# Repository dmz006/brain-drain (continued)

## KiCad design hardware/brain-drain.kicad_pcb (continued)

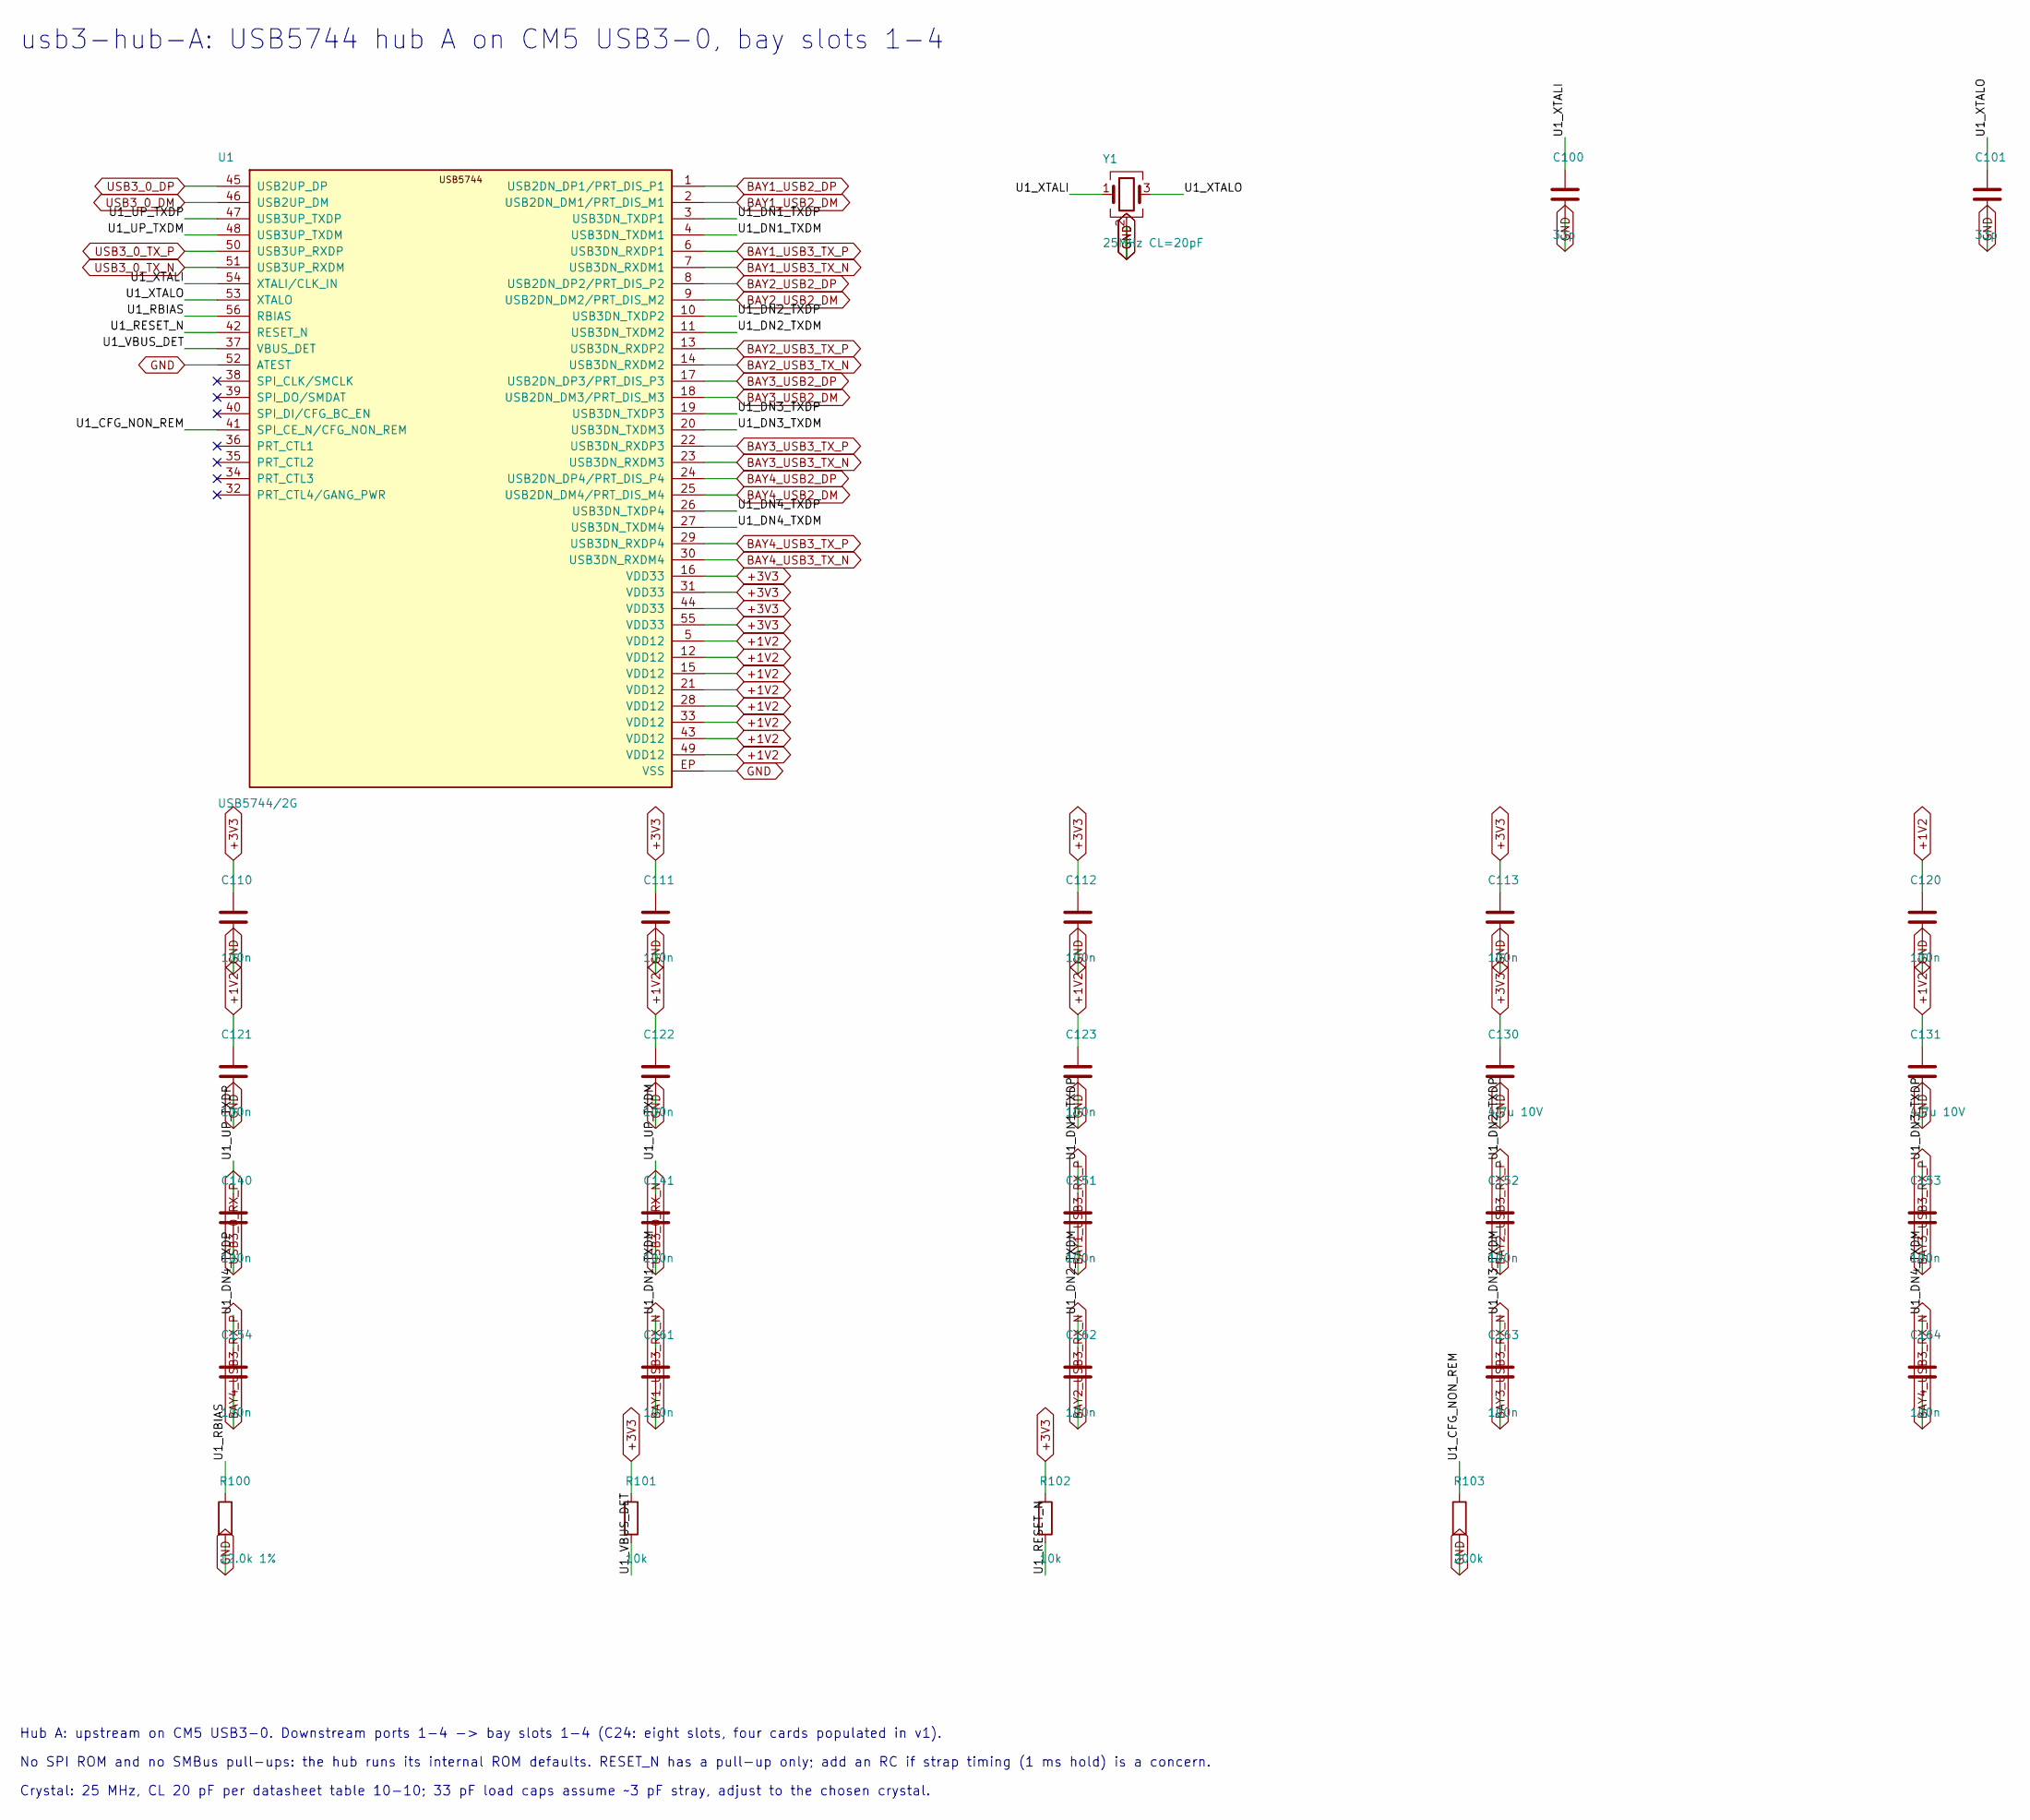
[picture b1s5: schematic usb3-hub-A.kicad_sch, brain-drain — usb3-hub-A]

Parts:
C100, C101: 33p; C_0402_1005Metric
C110, C111, C112, C113, C120, C121, C122, C123, C140, C141, C151, C152, C153, C154, C161, C162, C163, C164: 100n; C_0402_1005Metric
C130, C131: 4.7u 10V; C_0603_1608Metric
R100: 12.0k 1%; R_0402_1005Metric
R101, R102: 10k; R_0402_1005Metric
R103: 200k; R_0402_1005Metric
U1: USB5744/2G; QFN-56-1EP_7x7mm_P0.4mm_EP3.2x3.2mm
Y1: 25MHz CL=20pF; Crystal_SMD_3225-4Pin_3.2x2.5mm

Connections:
+1V2: C120.1, C121.1, C122.1, C123.1, C131.1, U1.5 (VDD12), U1.12 (VDD12), U1.15 (VDD12), U1.21 (VDD12), U1.28 (VDD12), U1.33 (VDD12), U1.43 (VDD12), U1.49 (VDD12); also elsewhere on the board
+3V3: C110.1, C111.1, C112.1, C113.1, C130.1, R101.1, R102.1, U1.16 (VDD33), U1.31 (VDD33), U1.44 (VDD33), U1.55 (VDD33); also elsewhere on the board
BAY1_USB2_DM: U1.2 (USB2DN_DM1/PRT_DIS_M1); also elsewhere on the board
BAY1_USB2_DP: U1.1 (USB2DN_DP1/PRT_DIS_P1); also elsewhere on the board
BAY1_USB3_RX_N: C161.2; also elsewhere on the board
BAY1_USB3_RX_P: C151.2; also elsewhere on the board
BAY1_USB3_TX_N: U1.7 (USB3DN_RXDM1); also elsewhere on the board
BAY1_USB3_TX_P: U1.6 (USB3DN_RXDP1); also elsewhere on the board
BAY2_USB2_DM: U1.9 (USB2DN_DM2/PRT_DIS_M2); also elsewhere on the board
BAY2_USB2_DP: U1.8 (USB2DN_DP2/PRT_DIS_P2); also elsewhere on the board
BAY2_USB3_RX_N: C162.2; also elsewhere on the board
BAY2_USB3_RX_P: C152.2; also elsewhere on the board
BAY2_USB3_TX_N: U1.14 (USB3DN_RXDM2); also elsewhere on the board
BAY2_USB3_TX_P: U1.13 (USB3DN_RXDP2); also elsewhere on the board
BAY3_USB2_DM: U1.18 (USB2DN_DM3/PRT_DIS_M3); also elsewhere on the board
BAY3_USB2_DP: U1.17 (USB2DN_DP3/PRT_DIS_P3); also elsewhere on the board
BAY3_USB3_RX_N: C163.2; also elsewhere on the board
BAY3_USB3_RX_P: C153.2; also elsewhere on the board
BAY3_USB3_TX_N: U1.23 (USB3DN_RXDM3); also elsewhere on the board
BAY3_USB3_TX_P: U1.22 (USB3DN_RXDP3); also elsewhere on the board
BAY4_USB2_DM: U1.25 (USB2DN_DM4/PRT_DIS_M4); also elsewhere on the board
BAY4_USB2_DP: U1.24 (USB2DN_DP4/PRT_DIS_P4); also elsewhere on the board
BAY4_USB3_RX_N: C164.2; also elsewhere on the board
BAY4_USB3_RX_P: C154.2; also elsewhere on the board
BAY4_USB3_TX_N: U1.30 (USB3DN_RXDM4); also elsewhere on the board
BAY4_USB3_TX_P: U1.29 (USB3DN_RXDP4); also elsewhere on the board
GND: C100.2, C101.2, C110.2, C111.2, C112.2, C113.2, C120.2, C121.2, C122.2, C123.2, C130.2, C131.2, R100.2, R103.2, U1.52 (ATEST), U1.EP (VSS), Y1.2 (G), Y1.4 (G); also elsewhere on the board
U1_CFG_NON_REM: R103.1, U1.41 (SPI_CE_N/CFG_NON_REM)
U1_DN1_TXDM: C161.1, U1.4 (USB3DN_TXDM1)
U1_DN1_TXDP: C151.1, U1.3 (USB3DN_TXDP1)
U1_DN2_TXDM: C162.1, U1.11 (USB3DN_TXDM2)
U1_DN2_TXDP: C152.1, U1.10 (USB3DN_TXDP2)
U1_DN3_TXDM: C163.1, U1.20 (USB3DN_TXDM3)
U1_DN3_TXDP: C153.1, U1.19 (USB3DN_TXDP3)
U1_DN4_TXDM: C164.1, U1.27 (USB3DN_TXDM4)
U1_DN4_TXDP: C154.1, U1.26 (USB3DN_TXDP4)
U1_RBIAS: R100.1, U1.56 (RBIAS)
U1_RESET_N: R102.2, U1.42 (RESET_N)
U1_UP_TXDM: C141.1, U1.48 (USB3UP_TXDM)
U1_UP_TXDP: C140.1, U1.47 (USB3UP_TXDP)
U1_VBUS_DET: R101.2, U1.37 (VBUS_DET)
U1_XTALI: C100.1, U1.54 (XTALI/CLK_IN), Y1.1
U1_XTALO: C101.1, U1.53 (XTALO), Y1.3
USB3_0_DM: U1.46 (USB2UP_DM); also elsewhere on the board
USB3_0_DP: U1.45 (USB2UP_DP); also elsewhere on the board
USB3_0_RX_N: C141.2; also elsewhere on the board
USB3_0_RX_P: C140.2; also elsewhere on the board
USB3_0_TX_N: U1.51 (USB3UP_RXDM); also elsewhere on the board
USB3_0_TX_P: U1.50 (USB3UP_RXDP); also elsewhere on the board

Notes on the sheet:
usb3-hub-A: USB5744 hub A on CM5 USB3-0, bay slots 1-4
Hub A: upstream on CM5 USB3-0. Downstream ports 1-4 -> bay slots 1-4 (C24: eight slots, four cards populated in v1).
No SPI ROM and no SMBus pull-ups: the hub runs its internal ROM defaults. RESET_N has a pull-up only; add an RC if strap timing (1 ms hold) is a concern.
Crystal: 25 MHz, CL 20 pF per datasheet table 10-10; 33 pF load caps assume ~3 pF stray, adjust to the chosen crystal.

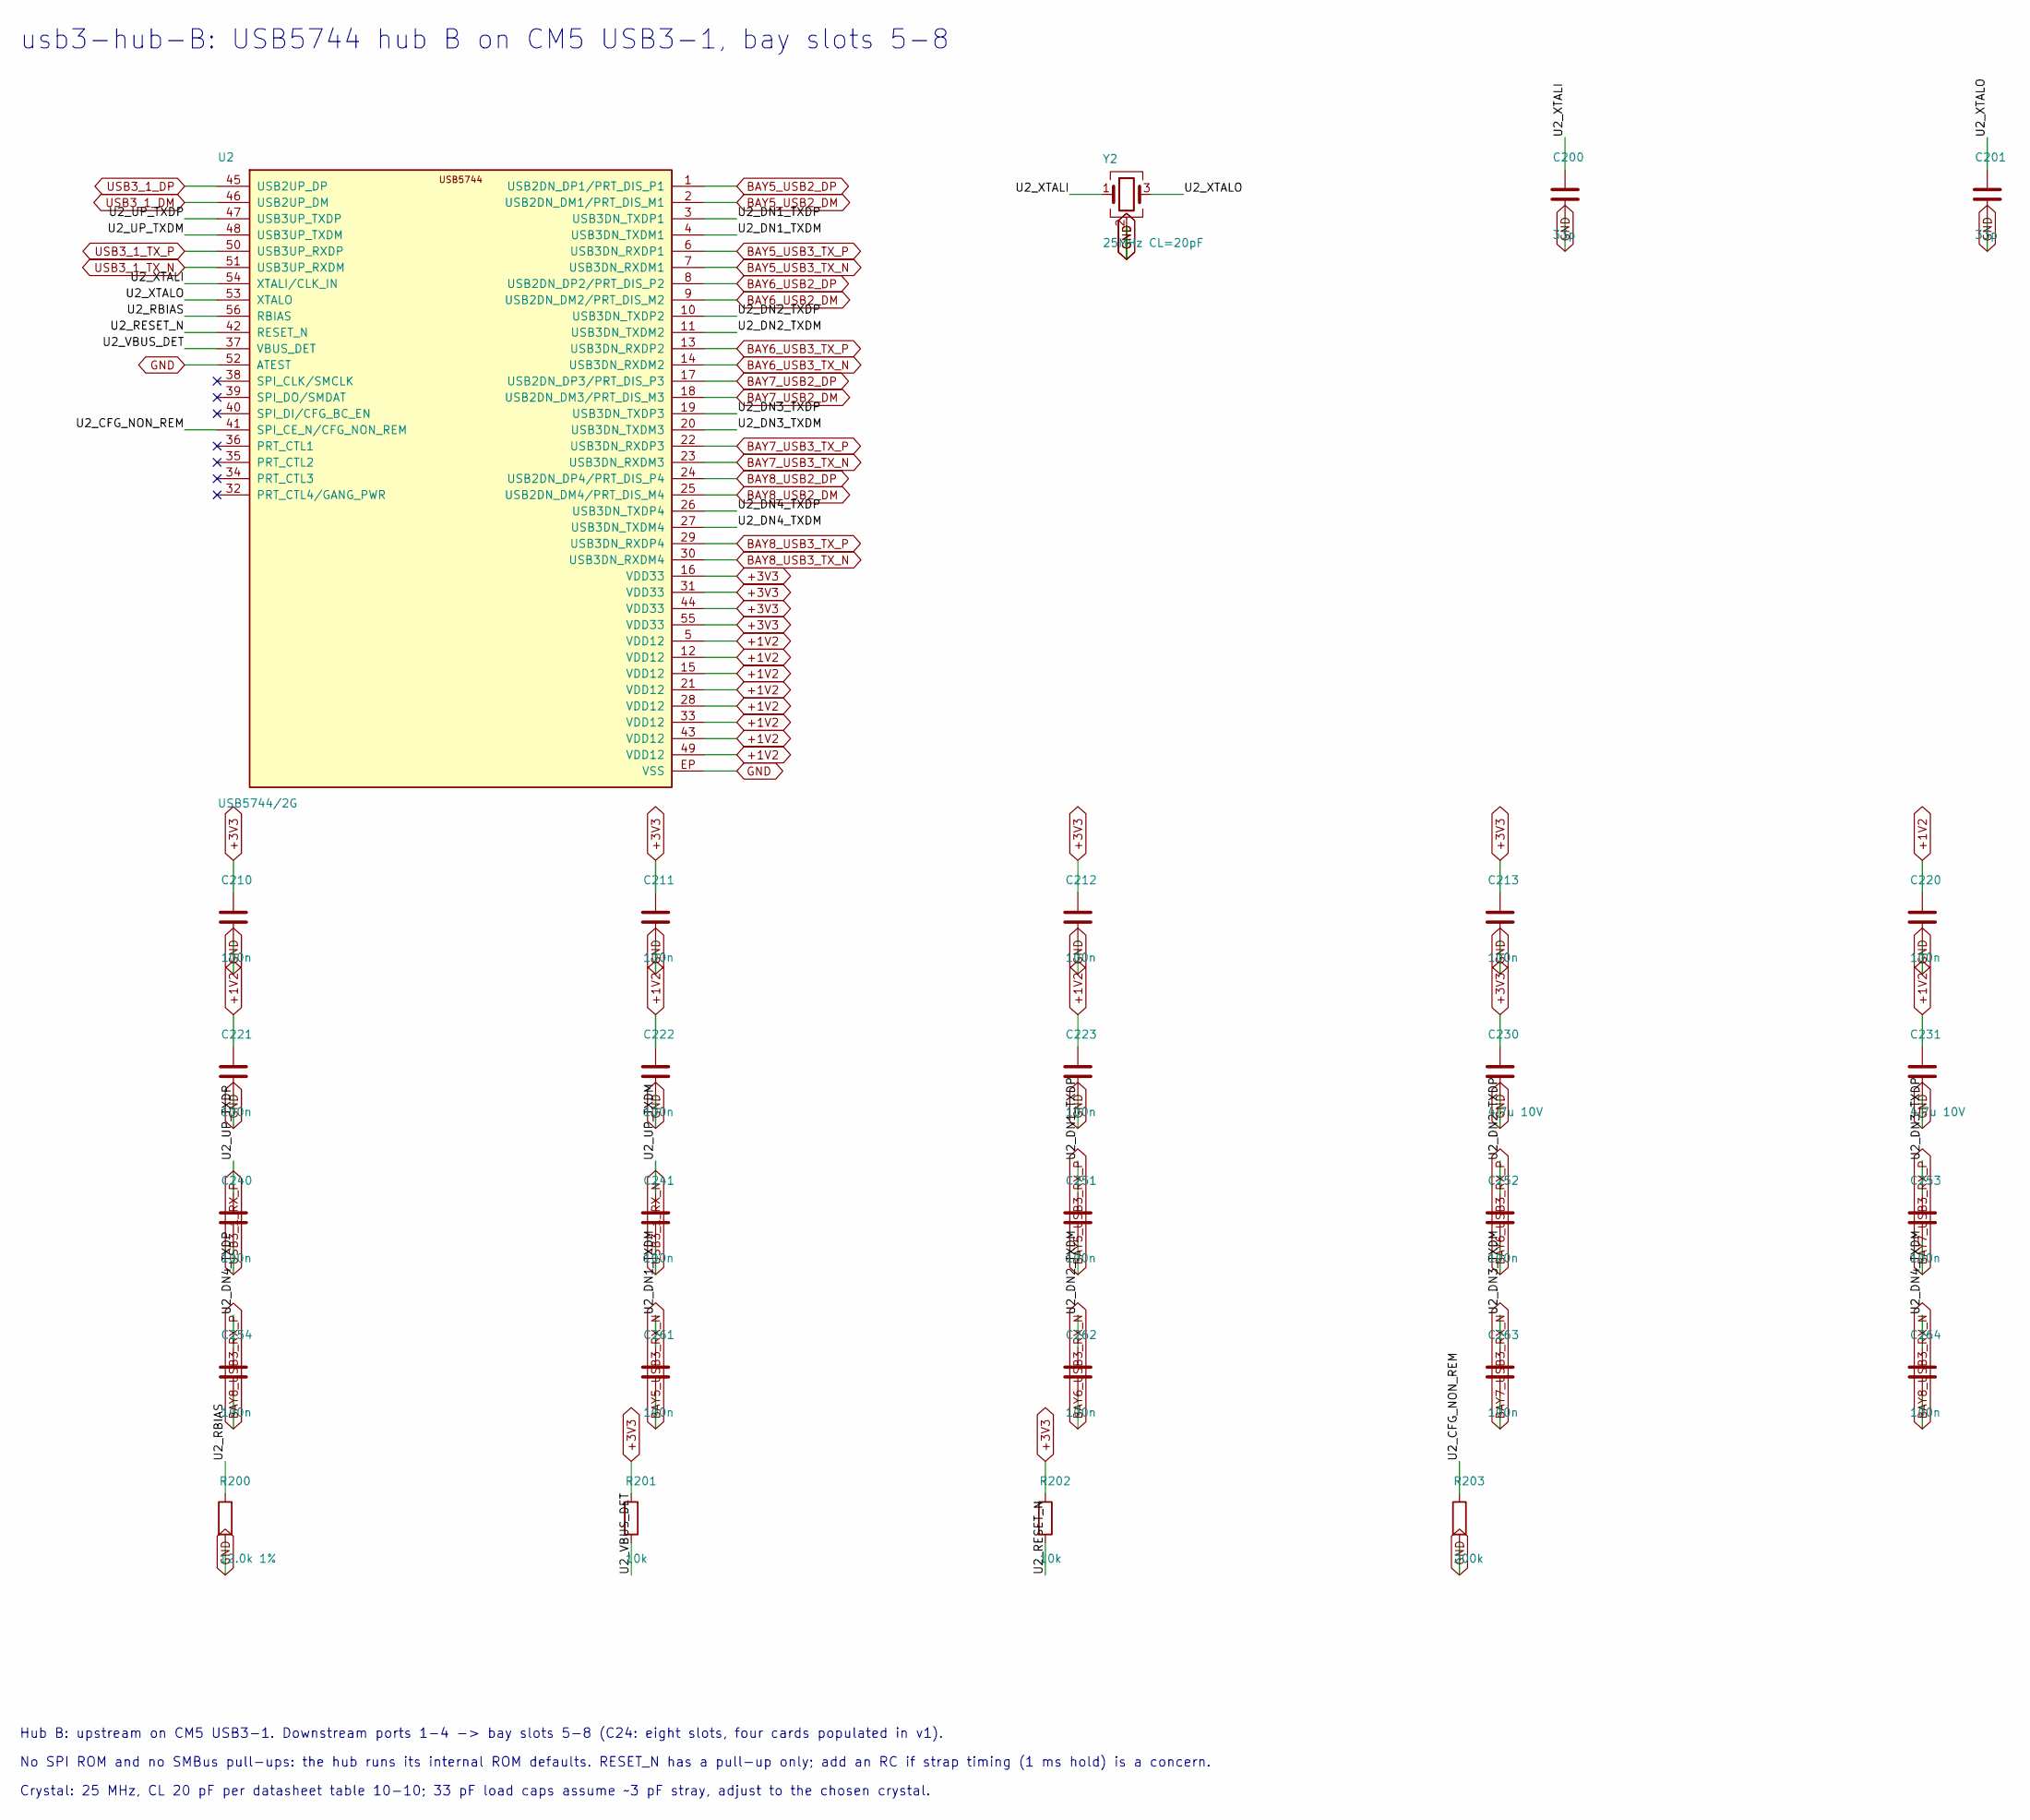
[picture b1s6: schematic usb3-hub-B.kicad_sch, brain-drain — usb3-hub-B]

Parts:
C200, C201: 33p; C_0402_1005Metric
C210, C211, C212, C213, C220, C221, C222, C223, C240, C241, C251, C252, C253, C254, C261, C262, C263, C264: 100n; C_0402_1005Metric
C230, C231: 4.7u 10V; C_0603_1608Metric
R200: 12.0k 1%; R_0402_1005Metric
R201, R202: 10k; R_0402_1005Metric
R203: 200k; R_0402_1005Metric
U2: USB5744/2G; QFN-56-1EP_7x7mm_P0.4mm_EP3.2x3.2mm
Y2: 25MHz CL=20pF; Crystal_SMD_3225-4Pin_3.2x2.5mm

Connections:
+1V2: C220.1, C221.1, C222.1, C223.1, C231.1, U2.5 (VDD12), U2.12 (VDD12), U2.15 (VDD12), U2.21 (VDD12), U2.28 (VDD12), U2.33 (VDD12), U2.43 (VDD12), U2.49 (VDD12); also elsewhere on the board
+3V3: C210.1, C211.1, C212.1, C213.1, C230.1, R201.1, R202.1, U2.16 (VDD33), U2.31 (VDD33), U2.44 (VDD33), U2.55 (VDD33); also elsewhere on the board
BAY5_USB2_DM: U2.2 (USB2DN_DM1/PRT_DIS_M1); also elsewhere on the board
BAY5_USB2_DP: U2.1 (USB2DN_DP1/PRT_DIS_P1); also elsewhere on the board
BAY5_USB3_RX_N: C261.2; also elsewhere on the board
BAY5_USB3_RX_P: C251.2; also elsewhere on the board
BAY5_USB3_TX_N: U2.7 (USB3DN_RXDM1); also elsewhere on the board
BAY5_USB3_TX_P: U2.6 (USB3DN_RXDP1); also elsewhere on the board
BAY6_USB2_DM: U2.9 (USB2DN_DM2/PRT_DIS_M2); also elsewhere on the board
BAY6_USB2_DP: U2.8 (USB2DN_DP2/PRT_DIS_P2); also elsewhere on the board
BAY6_USB3_RX_N: C262.2; also elsewhere on the board
BAY6_USB3_RX_P: C252.2; also elsewhere on the board
BAY6_USB3_TX_N: U2.14 (USB3DN_RXDM2); also elsewhere on the board
BAY6_USB3_TX_P: U2.13 (USB3DN_RXDP2); also elsewhere on the board
BAY7_USB2_DM: U2.18 (USB2DN_DM3/PRT_DIS_M3); also elsewhere on the board
BAY7_USB2_DP: U2.17 (USB2DN_DP3/PRT_DIS_P3); also elsewhere on the board
BAY7_USB3_RX_N: C263.2; also elsewhere on the board
BAY7_USB3_RX_P: C253.2; also elsewhere on the board
BAY7_USB3_TX_N: U2.23 (USB3DN_RXDM3); also elsewhere on the board
BAY7_USB3_TX_P: U2.22 (USB3DN_RXDP3); also elsewhere on the board
BAY8_USB2_DM: U2.25 (USB2DN_DM4/PRT_DIS_M4); also elsewhere on the board
BAY8_USB2_DP: U2.24 (USB2DN_DP4/PRT_DIS_P4); also elsewhere on the board
BAY8_USB3_RX_N: C264.2; also elsewhere on the board
BAY8_USB3_RX_P: C254.2; also elsewhere on the board
BAY8_USB3_TX_N: U2.30 (USB3DN_RXDM4); also elsewhere on the board
BAY8_USB3_TX_P: U2.29 (USB3DN_RXDP4); also elsewhere on the board
GND: C200.2, C201.2, C210.2, C211.2, C212.2, C213.2, C220.2, C221.2, C222.2, C223.2, C230.2, C231.2, R200.2, R203.2, U2.52 (ATEST), U2.EP (VSS), Y2.2 (G), Y2.4 (G); also elsewhere on the board
U2_CFG_NON_REM: R203.1, U2.41 (SPI_CE_N/CFG_NON_REM)
U2_DN1_TXDM: C261.1, U2.4 (USB3DN_TXDM1)
U2_DN1_TXDP: C251.1, U2.3 (USB3DN_TXDP1)
U2_DN2_TXDM: C262.1, U2.11 (USB3DN_TXDM2)
U2_DN2_TXDP: C252.1, U2.10 (USB3DN_TXDP2)
U2_DN3_TXDM: C263.1, U2.20 (USB3DN_TXDM3)
U2_DN3_TXDP: C253.1, U2.19 (USB3DN_TXDP3)
U2_DN4_TXDM: C264.1, U2.27 (USB3DN_TXDM4)
U2_DN4_TXDP: C254.1, U2.26 (USB3DN_TXDP4)
U2_RBIAS: R200.1, U2.56 (RBIAS)
U2_RESET_N: R202.2, U2.42 (RESET_N)
U2_UP_TXDM: C241.1, U2.48 (USB3UP_TXDM)
U2_UP_TXDP: C240.1, U2.47 (USB3UP_TXDP)
U2_VBUS_DET: R201.2, U2.37 (VBUS_DET)
U2_XTALI: C200.1, U2.54 (XTALI/CLK_IN), Y2.1
U2_XTALO: C201.1, U2.53 (XTALO), Y2.3
USB3_1_DM: U2.46 (USB2UP_DM); also elsewhere on the board
USB3_1_DP: U2.45 (USB2UP_DP); also elsewhere on the board
USB3_1_RX_N: C241.2; also elsewhere on the board
USB3_1_RX_P: C240.2; also elsewhere on the board
USB3_1_TX_N: U2.51 (USB3UP_RXDM); also elsewhere on the board
USB3_1_TX_P: U2.50 (USB3UP_RXDP); also elsewhere on the board

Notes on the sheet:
usb3-hub-B: USB5744 hub B on CM5 USB3-1, bay slots 5-8
Hub B: upstream on CM5 USB3-1. Downstream ports 1-4 -> bay slots 5-8 (C24: eight slots, four cards populated in v1).
No SPI ROM and no SMBus pull-ups: the hub runs its internal ROM defaults. RESET_N has a pull-up only; add an RC if strap timing (1 ms hold) is a concern.
Crystal: 25 MHz, CL 20 pF per datasheet table 10-10; 33 pF load caps assume ~3 pF stray, adjust to the chosen crystal.

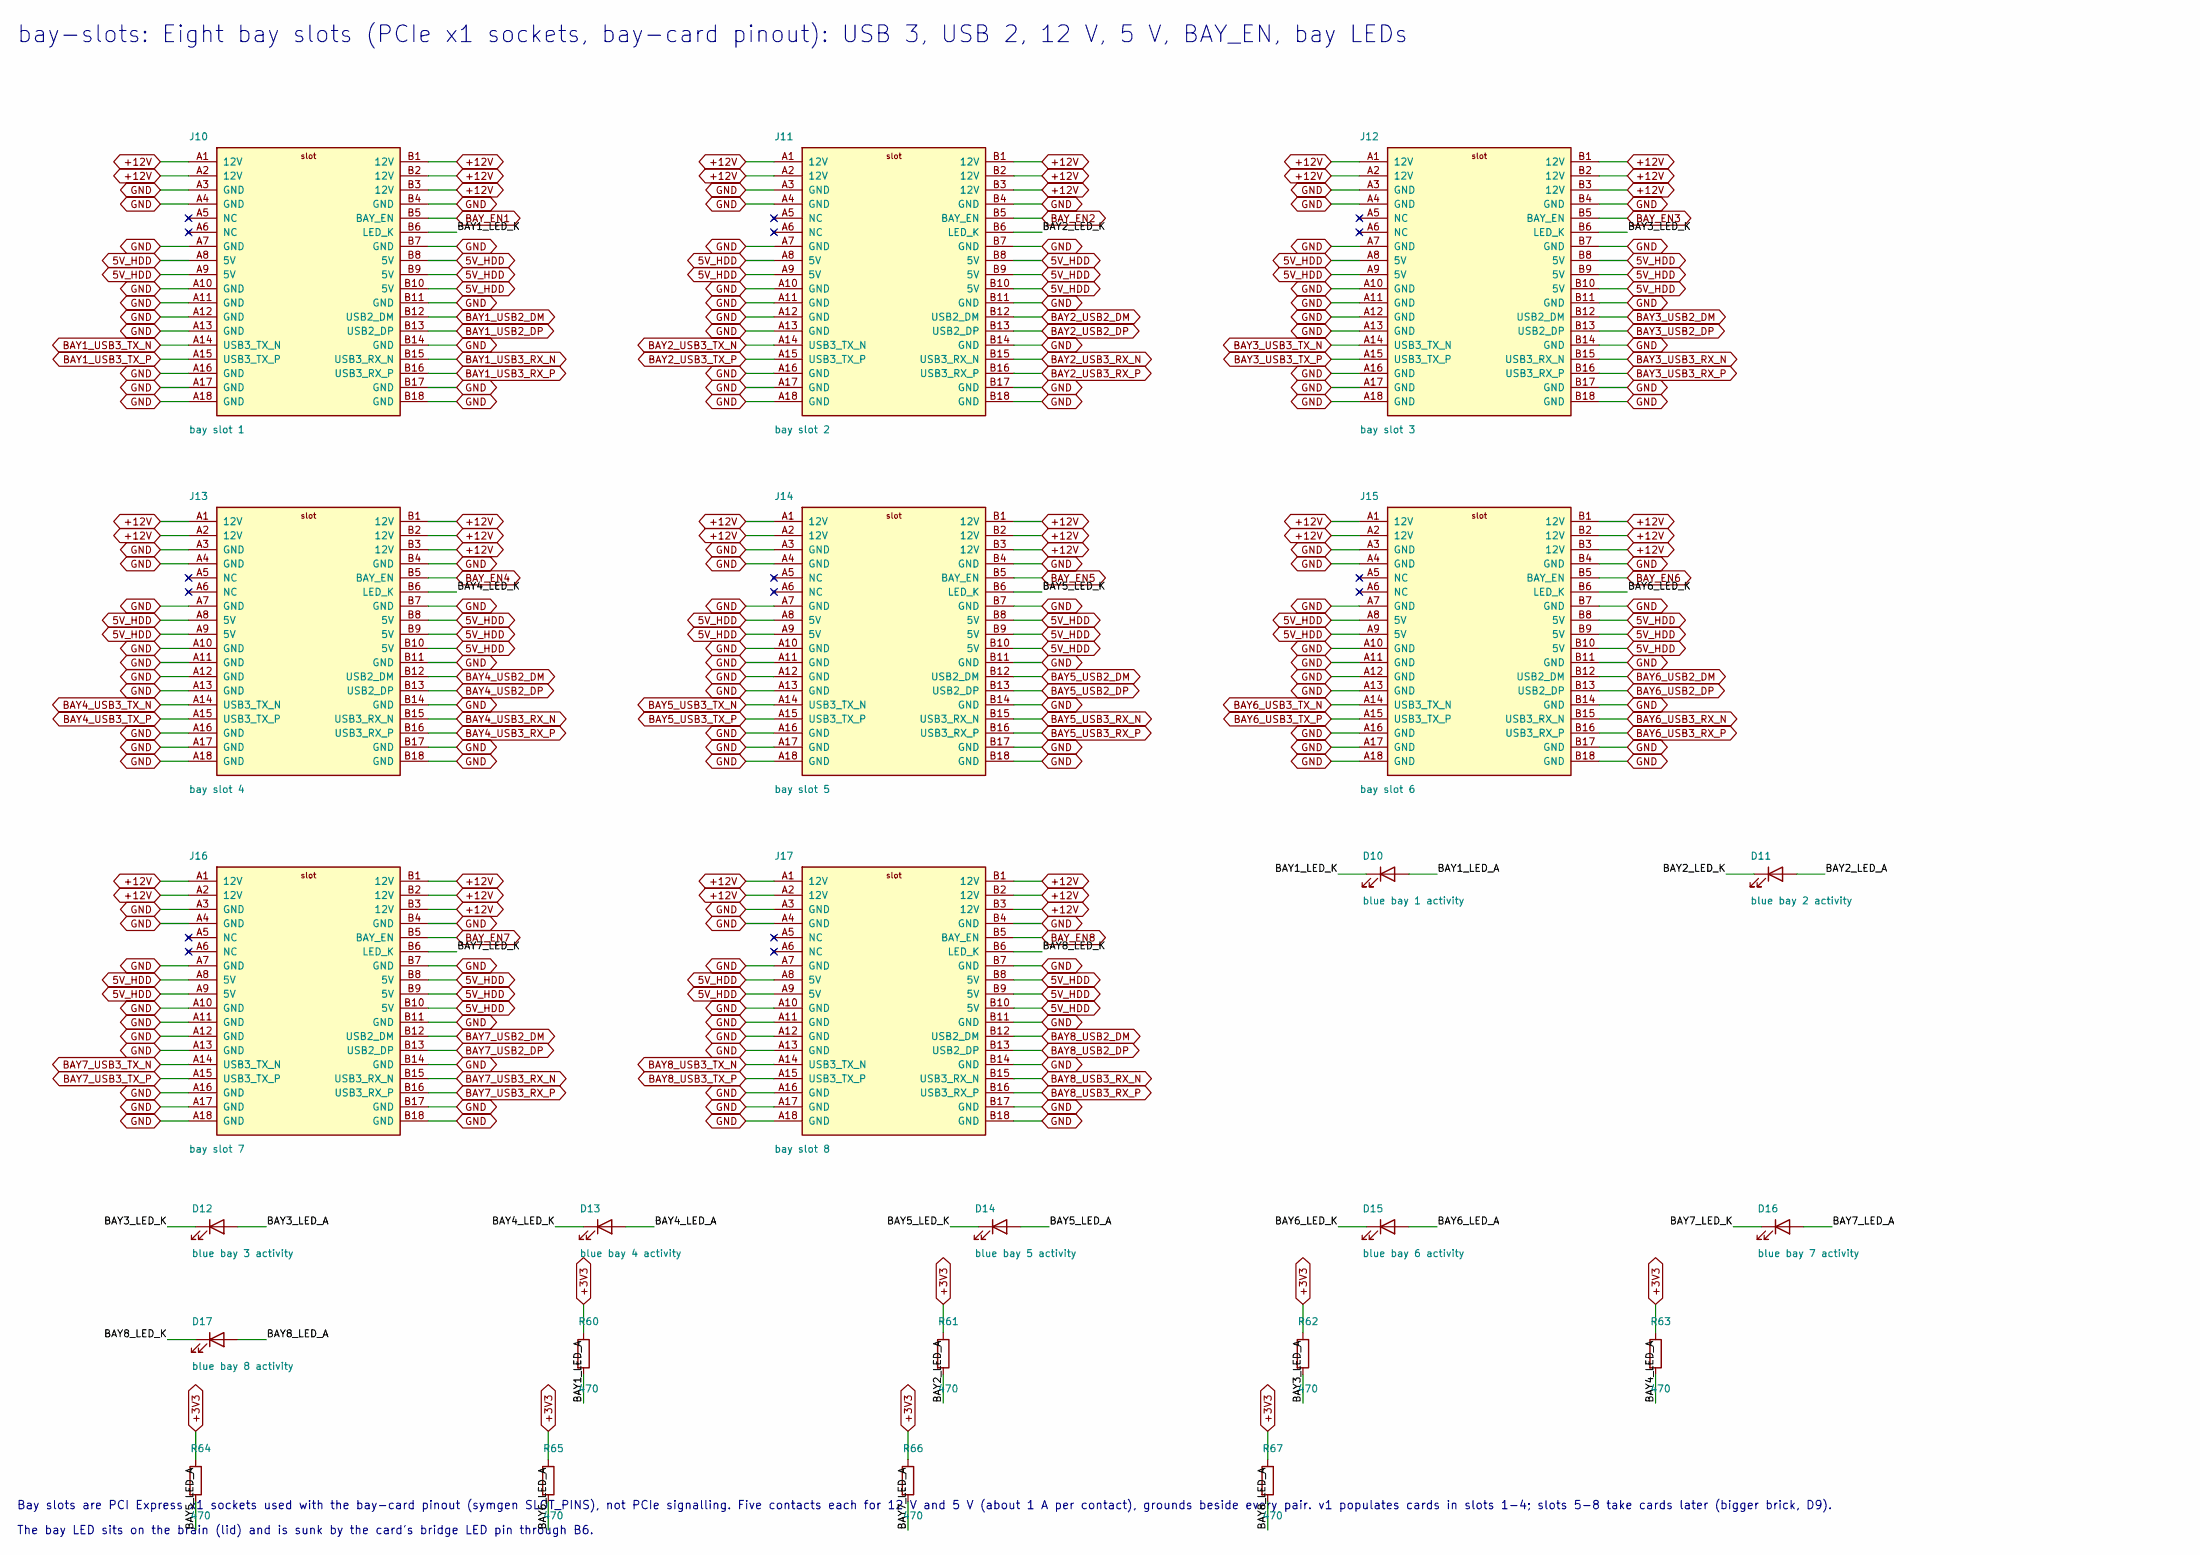
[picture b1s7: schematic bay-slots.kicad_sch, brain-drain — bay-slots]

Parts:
D10: blue bay 1 activity; LED_D3.0mm
D11: blue bay 2 activity; LED_D3.0mm
D12: blue bay 3 activity; LED_D3.0mm
D13: blue bay 4 activity; LED_D3.0mm
D14: blue bay 5 activity; LED_D3.0mm
D15: blue bay 6 activity; LED_D3.0mm
D16: blue bay 7 activity; LED_D3.0mm
D17: blue bay 8 activity; LED_D3.0mm
J10: bay slot 1; PCIe_x1_Socket_THT
J11: bay slot 2; PCIe_x1_Socket_THT
J12: bay slot 3; PCIe_x1_Socket_THT
J13: bay slot 4; PCIe_x1_Socket_THT
J14: bay slot 5; PCIe_x1_Socket_THT
J15: bay slot 6; PCIe_x1_Socket_THT
J16: bay slot 7; PCIe_x1_Socket_THT
J17: bay slot 8; PCIe_x1_Socket_THT
R60, R61, R62, R63, R64, R65, R66, R67: 470; R_0402_1005Metric

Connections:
5V_HDD: J10.A8 (5V), J10.A9 (5V), J10.B8 (5V), J10.B9 (5V), J10.B10 (5V), J11.A8 (5V), J11.A9 (5V), J11.B8 (5V), J11.B9 (5V), J11.B10 (5V), J12.A8 (5V), J12.A9 (5V), J12.B8 (5V), J12.B9 (5V), J12.B10 (5V), J13.A8 (5V), J13.A9 (5V), J13.B8 (5V), J13.B9 (5V), J13.B10 (5V), J14.A8 (5V), J14.A9 (5V), J14.B8 (5V), J14.B9 (5V), J14.B10 (5V), J15.A8 (5V), J15.A9 (5V), J15.B8 (5V), J15.B9 (5V), J15.B10 (5V), J16.A8 (5V), J16.A9 (5V), J16.B8 (5V), J16.B9 (5V), J16.B10 (5V), J17.A8 (5V), J17.A9 (5V), J17.B8 (5V), J17.B9 (5V), J17.B10 (5V); also elsewhere on the board
+3V3: R60.1, R61.1, R62.1, R63.1, R64.1, R65.1, R66.1, R67.1; also elsewhere on the board
+12V: J10.A1 (12V), J10.A2 (12V), J10.B1 (12V), J10.B2 (12V), J10.B3 (12V), J11.A1 (12V), J11.A2 (12V), J11.B1 (12V), J11.B2 (12V), J11.B3 (12V), J12.A1 (12V), J12.A2 (12V), J12.B1 (12V), J12.B2 (12V), J12.B3 (12V), J13.A1 (12V), J13.A2 (12V), J13.B1 (12V), J13.B2 (12V), J13.B3 (12V), J14.A1 (12V), J14.A2 (12V), J14.B1 (12V), J14.B2 (12V), J14.B3 (12V), J15.A1 (12V), J15.A2 (12V), J15.B1 (12V), J15.B2 (12V), J15.B3 (12V), J16.A1 (12V), J16.A2 (12V), J16.B1 (12V), J16.B2 (12V), J16.B3 (12V), J17.A1 (12V), J17.A2 (12V), J17.B1 (12V), J17.B2 (12V), J17.B3 (12V); also elsewhere on the board
BAY1_LED_A: D10.2 (A), R60.2
BAY1_LED_K: D10.1 (K), J10.B6 (LED_K)
BAY1_USB2_DM: J10.B12 (USB2_DM); also elsewhere on the board
BAY1_USB2_DP: J10.B13 (USB2_DP); also elsewhere on the board
BAY1_USB3_RX_N: J10.B15 (USB3_RX_N); also elsewhere on the board
BAY1_USB3_RX_P: J10.B16 (USB3_RX_P); also elsewhere on the board
BAY1_USB3_TX_N: J10.A14 (USB3_TX_N); also elsewhere on the board
BAY1_USB3_TX_P: J10.A15 (USB3_TX_P); also elsewhere on the board
BAY2_LED_A: D11.2 (A), R61.2
BAY2_LED_K: D11.1 (K), J11.B6 (LED_K)
BAY2_USB2_DM: J11.B12 (USB2_DM); also elsewhere on the board
BAY2_USB2_DP: J11.B13 (USB2_DP); also elsewhere on the board
BAY2_USB3_RX_N: J11.B15 (USB3_RX_N); also elsewhere on the board
BAY2_USB3_RX_P: J11.B16 (USB3_RX_P); also elsewhere on the board
BAY2_USB3_TX_N: J11.A14 (USB3_TX_N); also elsewhere on the board
BAY2_USB3_TX_P: J11.A15 (USB3_TX_P); also elsewhere on the board
BAY3_LED_A: D12.2 (A), R62.2
BAY3_LED_K: D12.1 (K), J12.B6 (LED_K)
BAY3_USB2_DM: J12.B12 (USB2_DM); also elsewhere on the board
BAY3_USB2_DP: J12.B13 (USB2_DP); also elsewhere on the board
BAY3_USB3_RX_N: J12.B15 (USB3_RX_N); also elsewhere on the board
BAY3_USB3_RX_P: J12.B16 (USB3_RX_P); also elsewhere on the board
BAY3_USB3_TX_N: J12.A14 (USB3_TX_N); also elsewhere on the board
BAY3_USB3_TX_P: J12.A15 (USB3_TX_P); also elsewhere on the board
BAY4_LED_A: D13.2 (A), R63.2
BAY4_LED_K: D13.1 (K), J13.B6 (LED_K)
BAY4_USB2_DM: J13.B12 (USB2_DM); also elsewhere on the board
BAY4_USB2_DP: J13.B13 (USB2_DP); also elsewhere on the board
BAY4_USB3_RX_N: J13.B15 (USB3_RX_N); also elsewhere on the board
BAY4_USB3_RX_P: J13.B16 (USB3_RX_P); also elsewhere on the board
BAY4_USB3_TX_N: J13.A14 (USB3_TX_N); also elsewhere on the board
BAY4_USB3_TX_P: J13.A15 (USB3_TX_P); also elsewhere on the board
BAY5_LED_A: D14.2 (A), R64.2
BAY5_LED_K: D14.1 (K), J14.B6 (LED_K)
BAY5_USB2_DM: J14.B12 (USB2_DM); also elsewhere on the board
BAY5_USB2_DP: J14.B13 (USB2_DP); also elsewhere on the board
BAY5_USB3_RX_N: J14.B15 (USB3_RX_N); also elsewhere on the board
BAY5_USB3_RX_P: J14.B16 (USB3_RX_P); also elsewhere on the board
BAY5_USB3_TX_N: J14.A14 (USB3_TX_N); also elsewhere on the board
BAY5_USB3_TX_P: J14.A15 (USB3_TX_P); also elsewhere on the board
BAY6_LED_A: D15.2 (A), R65.2
BAY6_LED_K: D15.1 (K), J15.B6 (LED_K)
BAY6_USB2_DM: J15.B12 (USB2_DM); also elsewhere on the board
BAY6_USB2_DP: J15.B13 (USB2_DP); also elsewhere on the board
BAY6_USB3_RX_N: J15.B15 (USB3_RX_N); also elsewhere on the board
BAY6_USB3_RX_P: J15.B16 (USB3_RX_P); also elsewhere on the board
BAY6_USB3_TX_N: J15.A14 (USB3_TX_N); also elsewhere on the board
BAY6_USB3_TX_P: J15.A15 (USB3_TX_P); also elsewhere on the board
BAY7_LED_A: D16.2 (A), R66.2
BAY7_LED_K: D16.1 (K), J16.B6 (LED_K)
BAY7_USB2_DM: J16.B12 (USB2_DM); also elsewhere on the board
BAY7_USB2_DP: J16.B13 (USB2_DP); also elsewhere on the board
BAY7_USB3_RX_N: J16.B15 (USB3_RX_N); also elsewhere on the board
BAY7_USB3_RX_P: J16.B16 (USB3_RX_P); also elsewhere on the board
BAY7_USB3_TX_N: J16.A14 (USB3_TX_N); also elsewhere on the board
BAY7_USB3_TX_P: J16.A15 (USB3_TX_P); also elsewhere on the board
BAY8_LED_A: D17.2 (A), R67.2
BAY8_LED_K: D17.1 (K), J17.B6 (LED_K)
BAY8_USB2_DM: J17.B12 (USB2_DM); also elsewhere on the board
BAY8_USB2_DP: J17.B13 (USB2_DP); also elsewhere on the board
BAY8_USB3_RX_N: J17.B15 (USB3_RX_N); also elsewhere on the board
BAY8_USB3_RX_P: J17.B16 (USB3_RX_P); also elsewhere on the board
BAY8_USB3_TX_N: J17.A14 (USB3_TX_N); also elsewhere on the board
BAY8_USB3_TX_P: J17.A15 (USB3_TX_P); also elsewhere on the board
BAY_EN1: J10.B5 (BAY_EN); also elsewhere on the board
BAY_EN2: J11.B5 (BAY_EN); also elsewhere on the board
BAY_EN3: J12.B5 (BAY_EN); also elsewhere on the board
BAY_EN4: J13.B5 (BAY_EN); also elsewhere on the board
BAY_EN5: J14.B5 (BAY_EN); also elsewhere on the board
BAY_EN6: J15.B5 (BAY_EN); also elsewhere on the board
BAY_EN7: J16.B5 (BAY_EN); also elsewhere on the board
BAY_EN8: J17.B5 (BAY_EN); also elsewhere on the board
GND: J10.A3 (GND), J10.A4 (GND), J10.A7 (GND), J10.A10 (GND), J10.A11 (GND), J10.A12 (GND), J10.A13 (GND), J10.A16 (GND), J10.A17 (GND), J10.A18 (GND), J10.B4 (GND), J10.B7 (GND), J10.B11 (GND), J10.B14 (GND), J10.B17 (GND), J10.B18 (GND), J11.A3 (GND), J11.A4 (GND), J11.A7 (GND), J11.A10 (GND), J11.A11 (GND), J11.A12 (GND), J11.A13 (GND), J11.A16 (GND), J11.A17 (GND), J11.A18 (GND), J11.B4 (GND), J11.B7 (GND), J11.B11 (GND), J11.B14 (GND), J11.B17 (GND), J11.B18 (GND), J12.A3 (GND), J12.A4 (GND), J12.A7 (GND), J12.A10 (GND), J12.A11 (GND), J12.A12 (GND), J12.A13 (GND), J12.A16 (GND), J12.A17 (GND), J12.A18 (GND), J12.B4 (GND), J12.B7 (GND), J12.B11 (GND), J12.B14 (GND), J12.B17 (GND), J12.B18 (GND), J13.A3 (GND), J13.A4 (GND), J13.A7 (GND), J13.A10 (GND), J13.A11 (GND), J13.A12 (GND), J13.A13 (GND), J13.A16 (GND), J13.A17 (GND), J13.A18 (GND), J13.B4 (GND), J13.B7 (GND), J13.B11 (GND), J13.B14 (GND), J13.B17 (GND), J13.B18 (GND), J14.A3 (GND), J14.A4 (GND), J14.A7 (GND), J14.A10 (GND), J14.A11 (GND), J14.A12 (GND), J14.A13 (GND), J14.A16 (GND), J14.A17 (GND), J14.A18 (GND), J14.B4 (GND), J14.B7 (GND), J14.B11 (GND), J14.B14 (GND), J14.B17 (GND), J14.B18 (GND), J15.A3 (GND), J15.A4 (GND), J15.A7 (GND), J15.A10 (GND), J15.A11 (GND), J15.A12 (GND), J15.A13 (GND), J15.A16 (GND), J15.A17 (GND), J15.A18 (GND), J15.B4 (GND), J15.B7 (GND), J15.B11 (GND), J15.B14 (GND), J15.B17 (GND), J15.B18 (GND), J16.A3 (GND), J16.A4 (GND), J16.A7 (GND), J16.A10 (GND), J16.A11 (GND), J16.A12 (GND), J16.A13 (GND), J16.A16 (GND), J16.A17 (GND), J16.A18 (GND), J16.B4 (GND), J16.B7 (GND), J16.B11 (GND), J16.B14 (GND), J16.B17 (GND), J16.B18 (GND), J17.A3 (GND), J17.A4 (GND), J17.A7 (GND), J17.A10 (GND), J17.A11 (GND), J17.A12 (GND), J17.A13 (GND), J17.A16 (GND), J17.A17 (GND), J17.A18 (GND), J17.B4 (GND), J17.B7 (GND), J17.B11 (GND), J17.B14 (GND), J17.B17 (GND), J17.B18 (GND); also elsewhere on the board

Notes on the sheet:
bay-slots: Eight bay slots (PCIe x1 sockets, bay-card pinout): USB 3, USB 2, 12 V, 5 V, BAY_EN, bay LEDs
Bay slots are PCI Express x1 sockets used with the bay-card pinout (symgen SLOT_PINS), not PCIe signalling. Five contacts each for 12 V and 5 V (about 1 A per contact), grounds beside every pair. v1 populates cards in slots 1-4; slots 5-8 take cards later (bigger brick, D9).
The bay LED sits on the brain (lid) and is sunk by the card's bridge LED pin through B6.
